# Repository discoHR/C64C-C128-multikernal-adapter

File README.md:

# C64-C128-28pin-multi-kernal-adapter
Multi-karnal adapter for C64 and C128

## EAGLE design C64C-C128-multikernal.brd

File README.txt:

C64C/C128 Switchless Multi-Kernal Adapter
27C512/27C256 ROM adapter for C64C and C128
https://github.com/discoHR/C64C-C128-multikernal-adapter
Designed by discoHR, based on Bwack's 24-pin adapter design.
(https://github.com/bwack/C64-Switchless-Multi-Kernal-27C256-adapter)
CERN OPEN HARDWARE LICENSE v1.2
http://www.ohwr.org/

It allows you to run either:
a) four kernals using a 27C512 (SJ1 open)
b) two kernals using a 27C256 (SJ1 closed)

Hold the restore key to enter the select mode. You will notice a fast flash
on the LED. Release the restore key when the flashing stops and press it
shortly as many times as you want to switch to the other kernals.
The LED colour will indicate which kernal is selected.
The C64 will reset to selected kernal shortly after you stop pressing the
restore key.

The Reset button (if present) behaves similar to the restore key but
unlike the restore key, the reset button is always in select mode.

There are two LED colour themes but due to hardware limitations, they don't
differ much. You can hold the restore key during power-on to toggle between
the two themes.

Theme #1:
2 kernals: yellow, blue
4 kernals: red, blue, green, cyan

Theme #2:
2 kernals: orange, magenta
4 kernals: red, magenta, lime, white

For R1, R2 and R3 you can use any value up to 12k (perhaps even more), depends
how bright you want the RGB LED.

Changelog:

Firmware udpates (PCB agnostic)

2016-10-23
- using sleep and IOC

PCB rev1.1 (final)

2016-10-02
- expanded the pcb a bit
- increased the distance between EPROM and connectors
- increased font sizes
- moved some texts to the bottom
- added CERN OHL and GitHub URL to the silkscreen
- finalized rev1.1

2016-09-30
- first version of firmware

2016-09-28
- swapped BLUE and GREEN signals to match the RGB LED pinout
- using 6.7k value for R1, R2 and R3

2016-09-19
- bumped resistor values significantly because the LED is still too bright at 6.7k
- increased the board size a bit and rerouted most of the traces

2016-09-18
- added license
- moved pin headers to the bottom where they belong
- using larger pads

PCB rev1.0 (final)

2016-09-17
- added board images and PDF with schematic
- minor aesthetic changes on the silk layer

2016-09-15
- removed R4
- rearranged signal-pin pairs to allow using weak pull-up for the solder jumper
- minor design changes
- improved routing
- fixed incorrectly connected switch
- moved everything from _tsilk to tNames layer

2016-09-14
- added NC next to unconnected pin
- initial commit

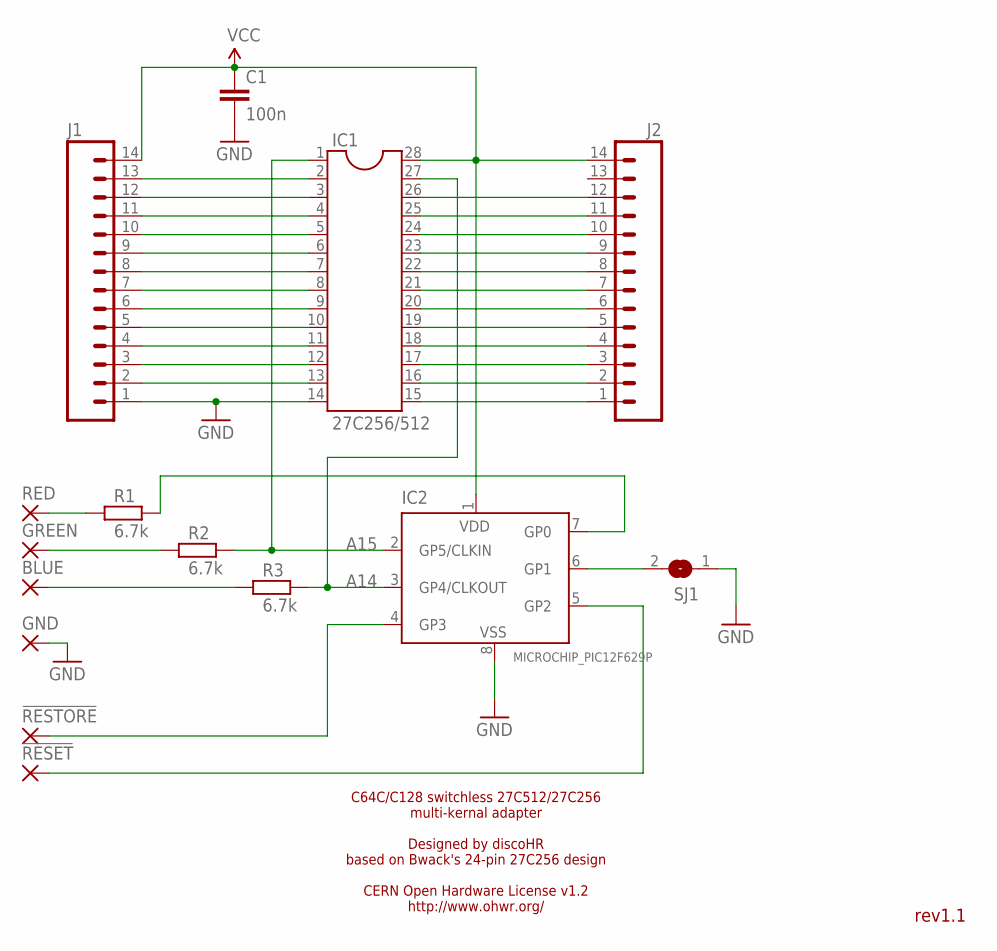
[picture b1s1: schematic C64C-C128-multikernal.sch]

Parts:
!RESET!: 2,15/1,0
!RESTORE!: 2,15/1,0
BLUE: 2,15/1,0
C1: 100n; C025-024X044
GND: 2,15/1,0
GREEN: 2,15/1,0
IC1: 27C256/512; IC-PACKAGE_EDIT_DIL28SPECIAL
IC2: MICROCHIP_PIC12F629P; MICROCHIP_DIL8
J1, J2: M14; 1X14
R1, R2, R3: 6.7k; RCL_0207/10
RED: 2,15/1,0
SJ1: SJ

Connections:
A14: IC1.27, IC2.3 (GP4/CLKOUT), R3.2
A15: IC1.1, IC2.2 (GP5/CLKIN), R2.2
GND: C1.2, GND.1, IC1.14, IC2.8 (VSS), J1.1, SJ1.1
unnamed: IC2.7 (GP0), R1.2
unnamed: R1.1, RED.1
unnamed: IC1.15, J2.1
unnamed: IC1.16, J2.2
unnamed: IC1.17, J2.3
unnamed: IC1.18, J2.4
unnamed: IC1.19, J2.5
unnamed: IC1.20, J2.6
unnamed: IC1.21, J2.7
unnamed: IC1.22, J2.8
unnamed: IC1.23, J2.9
unnamed: IC1.24, J2.10
unnamed: IC1.25, J2.11
unnamed: IC1.26, J2.12
unnamed: IC1.2, J1.13
unnamed: IC2.6 (GP1), SJ1.2
unnamed: IC1.3, J1.12
unnamed: IC1.4, J1.11
unnamed: IC1.5, J1.10
unnamed: IC1.6, J1.9
unnamed: IC1.7, J1.8
unnamed: IC1.8, J1.7
unnamed: IC1.9, J1.6
unnamed: IC1.10, J1.5
unnamed: IC1.11, J1.4
unnamed: IC1.12, J1.3
unnamed: IC1.13, J1.2
unnamed: !RESET!.1, IC2.5 (GP2)
unnamed: GREEN.1, R2.1
unnamed: BLUE.1, R3.1
unnamed: !RESTORE!.1, IC2.4 (GP3)
VCC: C1.1, IC1.28, IC2.1 (VDD), J1.14, J2.14

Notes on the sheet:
C64C/C128 switchless 27C512/27C256 multi-kernal adapter Designed by discoHR based on Bwack's 24-pin 27C256 design CERN Open Hardware License v1.2 http://www.ohwr.org/
rev1.1

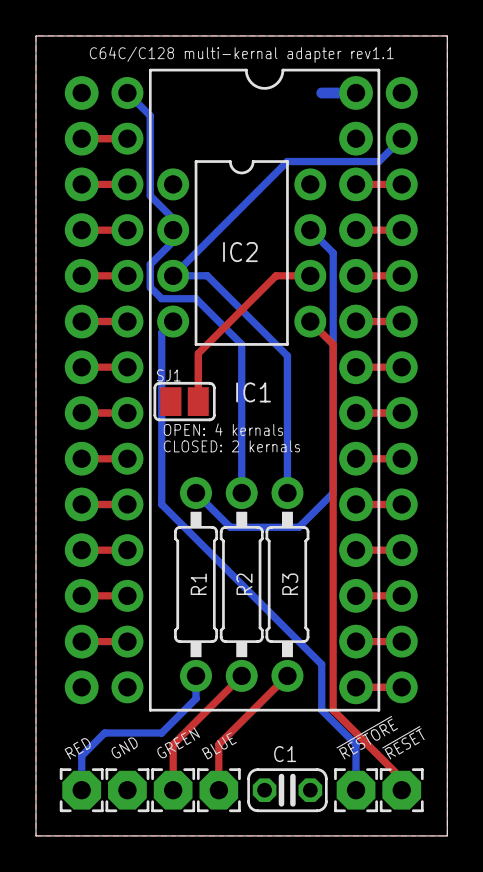
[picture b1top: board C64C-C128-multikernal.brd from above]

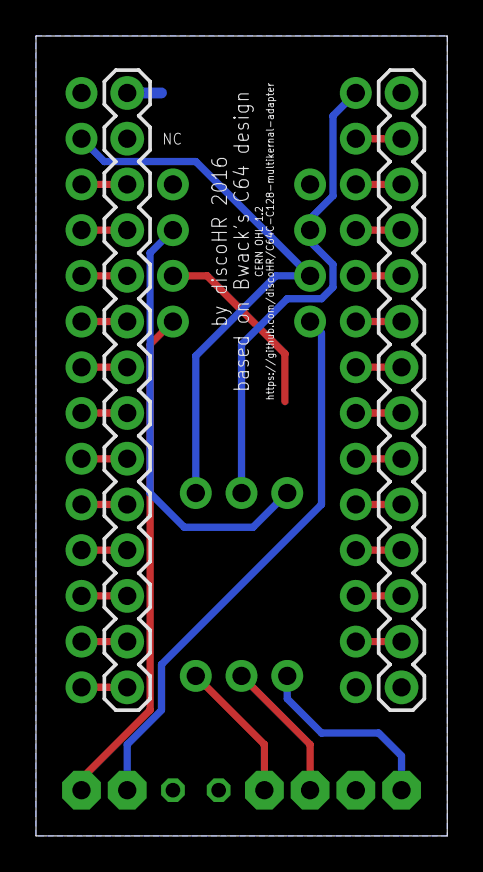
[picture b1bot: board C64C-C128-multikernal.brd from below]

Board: 2 copper layers, 22.8 x 44.4 mm, 15 parts (2 on the bottom side), 35 nets.

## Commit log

2016-09-14 init
2016-09-14 cleanup
2016-09-14 added NC next to unconnected pin
2016-09-14 added NC next to the unconnected pin
2016-09-14 removed R4 rearranged signal-pin pairs to allow using weak pull-up for the solder jumper minor design changes improved routing
2016-09-15 fixed incorrectly connected switch
2016-09-15 moved everything from _tsilk to tNames layer
2016-09-17 added board images and PDF with schematic minor aesthetic changes on the silk layer
2016-09-18 added license
2016-09-18 moved pin headers to the bottom where they belong
2016-09-18 using larger pads
2016-09-18 added license to schematic
2016-09-18 oops
2016-09-19 bumped resistor values significantly because the LED is still too bright at 6.7k increased the board size a bit and rerouted most of the traces
2016-09-28 swapped BLUE and GREEN signals to match the RGB LED pinout
2016-09-28 using 6.7k value for R1, R2 and R3
2016-09-30 first version of firmware
2016-09-30 testing in progress
2016-09-30 colour update
2016-10-01 updated test results
2016-10-02 expanded the pcb a bit increased the distance between EPROM and connectors increased font sizes moved some texts to the bottom added CERN OHL and GitHub URL to the silkscreen finalized rev1.1
2016-10-02 updated readme.txt
2016-10-17 tested with 27C512 on C64C
2016-10-23 using sleep and IOC
2016-12-13 removed disclaimer as it was tested in all configurations

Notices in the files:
C64C-C128-multikernal.brd:
CERN OHL 1.2
parts and their libraries:
SparkFun-Connectors: Licensing: Creative Commons ShareAlike 4.0 International - https://creativecommons.org/licenses/by-sa/4.0
